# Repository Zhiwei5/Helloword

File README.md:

Hi everyone,

   Here is the README file for this light bulb project.

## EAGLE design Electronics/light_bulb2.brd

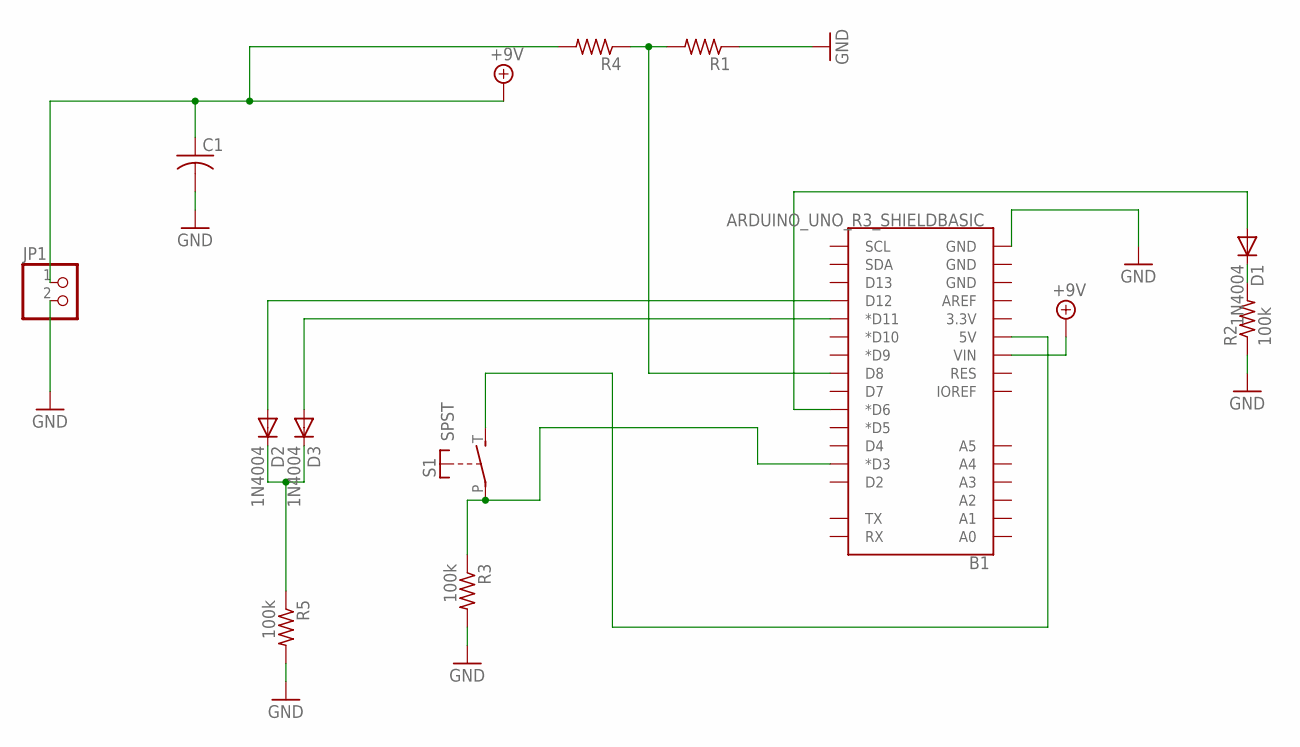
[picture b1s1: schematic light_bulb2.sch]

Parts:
B1: ARDUINO_UNO_R3_SHIELDBASIC; UNO_R3_SHIELD
C1: 0.1; C0805
D1, D2, D3: 1N4004; DO41-10
JP1: PINHD-1X2; 1X02
R1: 15k; R0805
R2, R3, R5: 100k; R0805
R4: 20k; R0805
S1: SPST; JUDCOSPST

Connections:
+9V: B1.VIN, C1.1, JP1.1, R4.2
GND: B1.GND@0 (GND), C1.2, JP1.2, R1.1, R2.1, R3.2, R5.2
unnamed: B1.5V, S1.T (S)
unnamed: D1.C, R2.2
unnamed: B1.D8, R1.2, R4.1
unnamed: B1.D3 (*D3), R3.1, S1.P
unnamed: B1.D6 (*D6), D1.A
unnamed: B1.D12, D2.A
unnamed: B1.D11 (*D11), D3.A
unnamed: D2.C, D3.C, R5.1

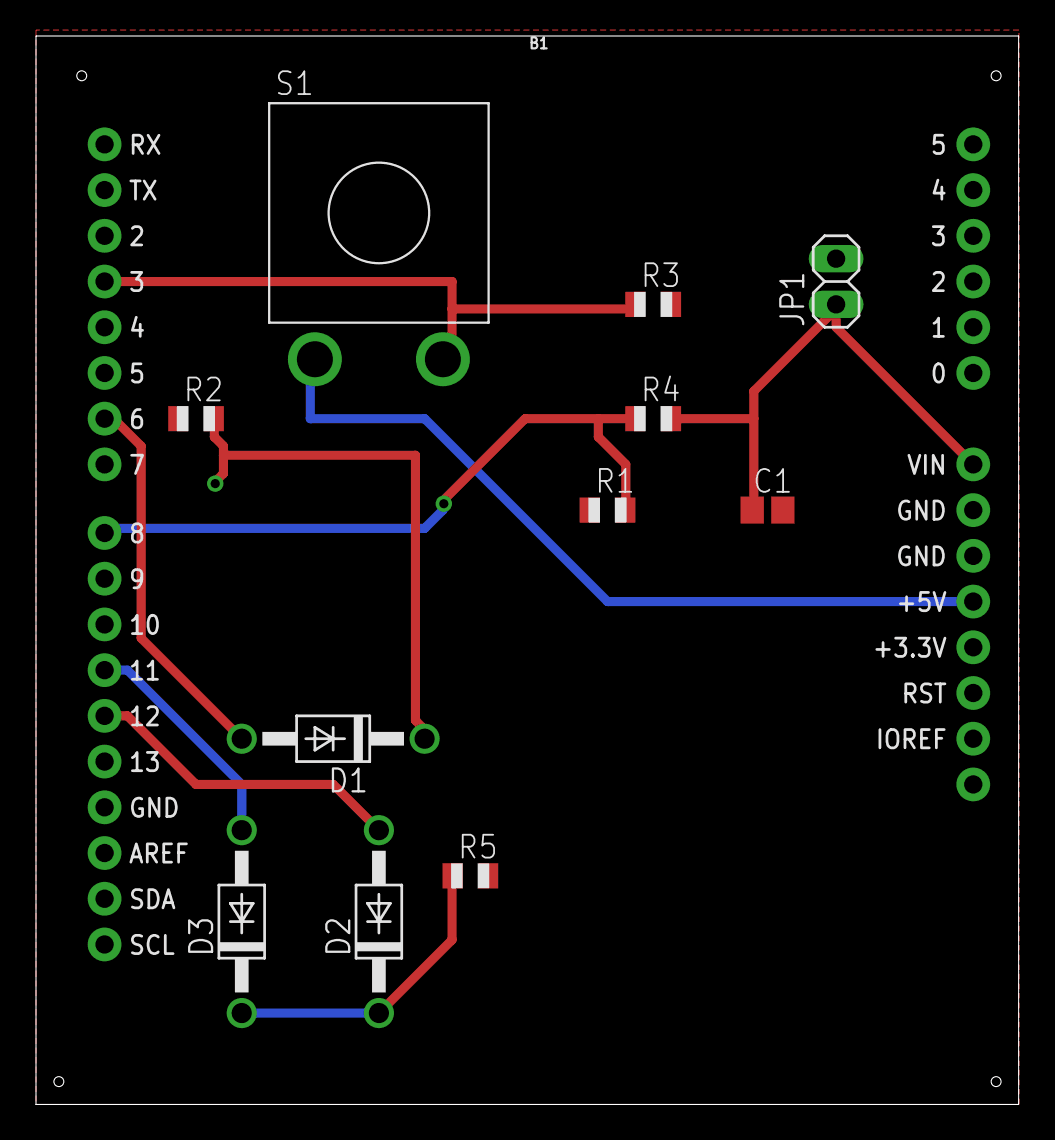
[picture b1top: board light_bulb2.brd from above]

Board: 2 copper layers, 54.6 x 59.4 mm, 12 parts (0 on the bottom side), 10 nets.

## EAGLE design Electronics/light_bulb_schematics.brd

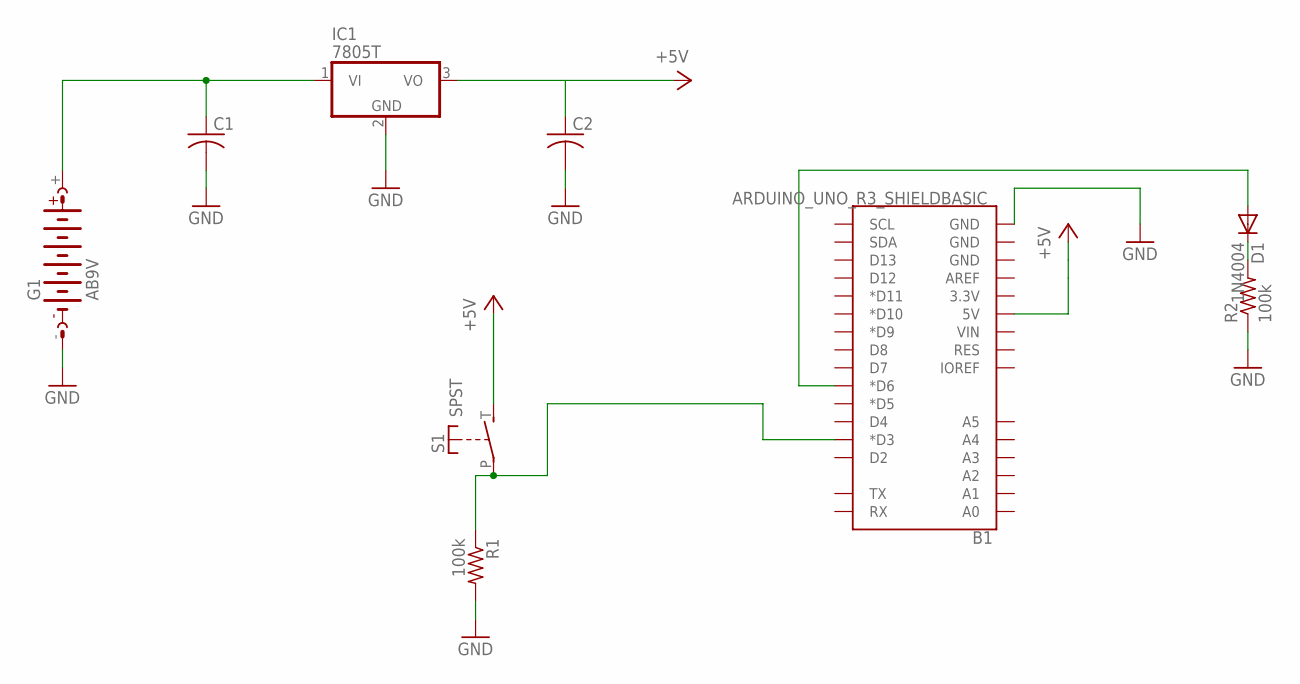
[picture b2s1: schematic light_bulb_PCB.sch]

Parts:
B1: ARDUINO_UNO_R3_SHIELDBASIC; UNO_R3_SHIELD
C1, C2: 0.1; C0805
D1: 1N4004; DO41-10
G1: AB9V
IC1: 7805T; TO220H
R1, R2: 100k; R0805
S1: SPST; JUDCOSPST

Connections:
+5V: B1.5V, C2.1, IC1.3 (VO), S1.T (S)
GND: B1.GND@0 (GND), C1.2, C2.2, G1.-, IC1.2 (GND), R1.2, R2.1
unnamed: C1.1, G1.+, IC1.1 (VI)
unnamed: D1.C, R2.2
unnamed: B1.D3 (*D3), R1.1, S1.P
unnamed: B1.D6 (*D6), D1.A

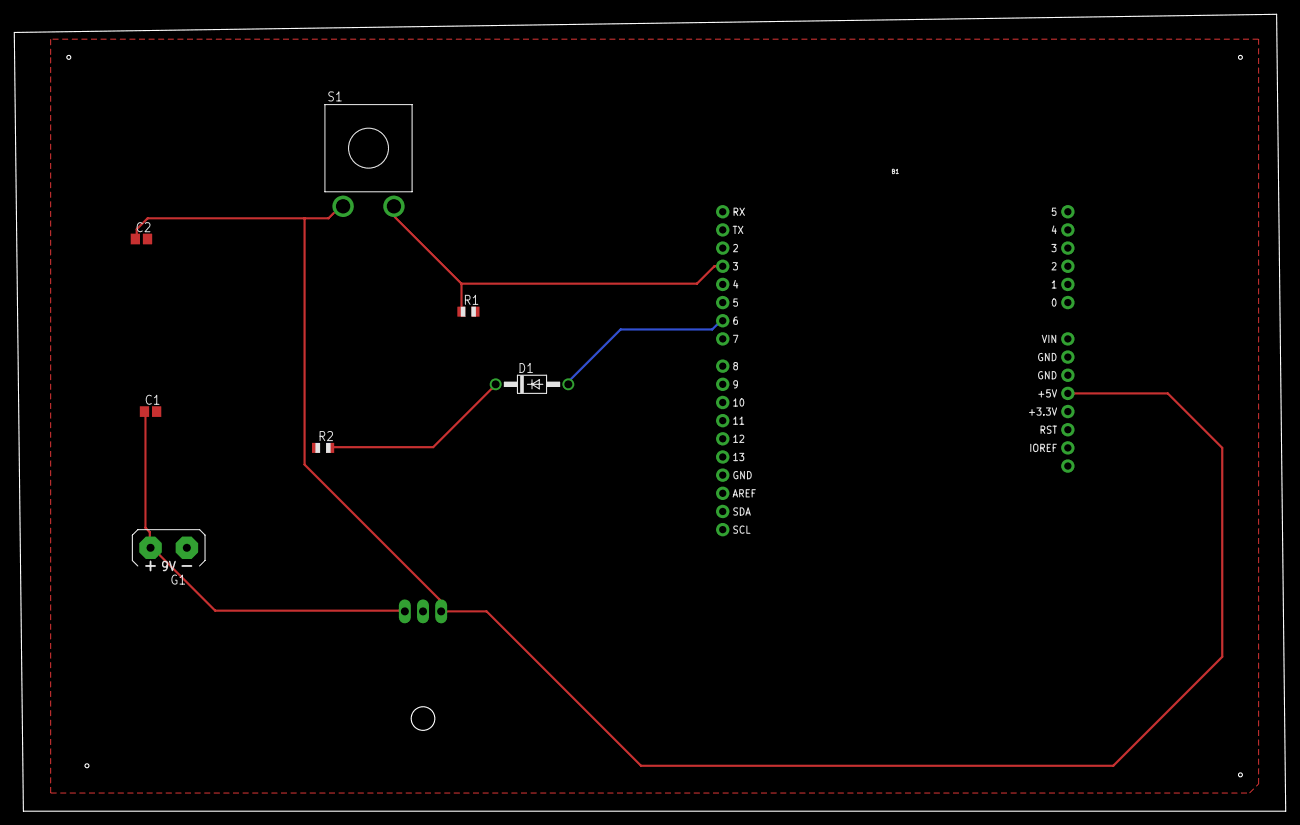
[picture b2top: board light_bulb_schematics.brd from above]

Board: 2 copper layers, 177.8 x 111.4 mm, 9 parts (1 on the bottom side), 6 nets.

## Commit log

2018-11-02 Milestone 03
2018-11-08 milestone04
2018-11-12 add ECAD file for review
2018-11-18 mechanical 01
2018-12-03 update the eletronics design
2018-12-12 final mechanical design
2018-12-12 final software design
2018-12-13 final components lists
2018-12-13 final schematic pdf
2018-12-13 3d pdf of Base

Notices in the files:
parts and their libraries:
SparkFun-Boards: Licensing: Creative Commons ShareAlike 4.0 International - https://creativecommons.org/licenses/by-sa/4.0
